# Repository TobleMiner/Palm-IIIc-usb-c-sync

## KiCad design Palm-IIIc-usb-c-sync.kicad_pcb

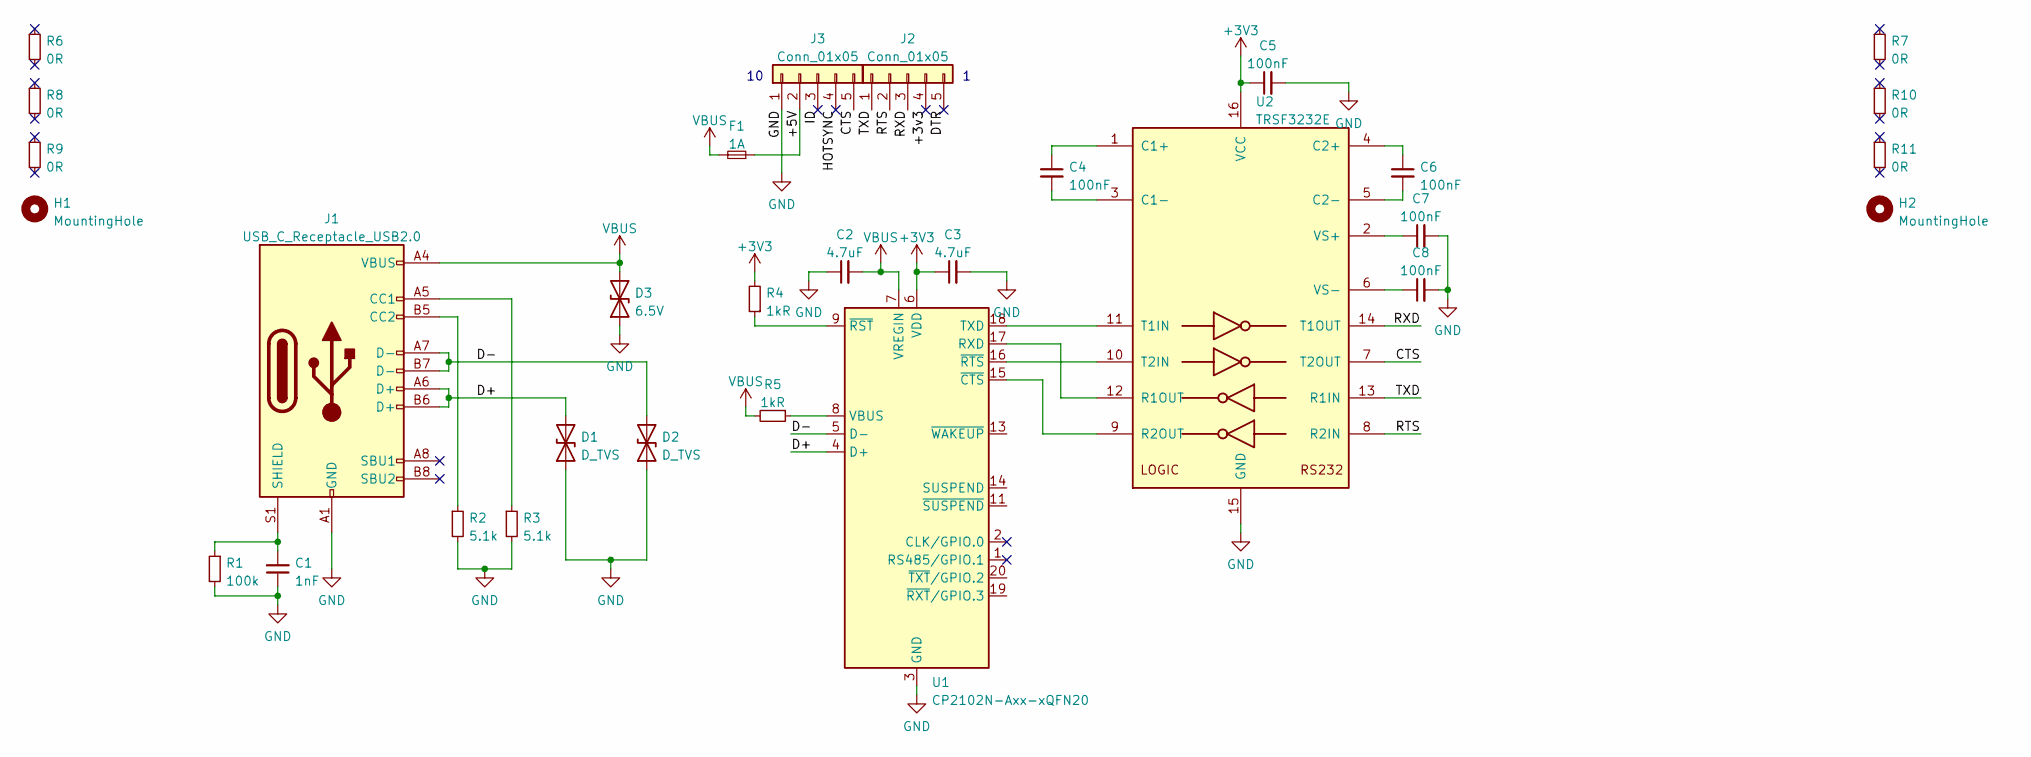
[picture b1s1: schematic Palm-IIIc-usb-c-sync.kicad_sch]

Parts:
C1: 1nF; C_0603_1608Metric; LCSC C1588
C2, C3: 4.7uF; C_0402_1005Metric; LCSC C23733
C4, C5, C6, C7, C8: 100nF; C_0402_1005Metric; LCSC C1525
D1, D2: D_TVS; C_0402_1005Metric; LCSC C125059
D3: 6.5V; D_SOD-523; LCSC C506103
F1: 1A; Fuse_0402_1005Metric; LCSC C424347
H1, H2: MountingHole; ToolingHole_JLCSMT
J1: USB_C_Receptacle_USB2.0; MC-311S; LCSC C2977718
J2, J3: Conn_01x05; 05x01_2mm
R1: 100k; R_0603_1608Metric; LCSC C25803
R2, R3: 5.1k; R_0402_1005Metric; LCSC C25905
R4, R5: 1kR; R_0402_1005Metric; LCSC C11702
R6, R7, R8, R9, R10, R11: 0R; R_0603_1608Metric; LCSC C21189
U1: CP2102N-Axx-xQFN20; SilivonLabs_QFN-20-1EP_3x3mm_P0.5mm_missing_pads; LCSC C969913
U2: TRSF3232E; TSSOP-16_4.4x5mm_P0.65mm; LCSC C2671080

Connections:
+3V3: C3.1, C5.1, R4.2, U1.6 (VDD), U2.16 (VCC)
/+3v3: J2.4
/+5V: F1.1, J3.2
/CTS: J3.5, U2.7 (T2OUT)
/D+: D1.2 (A2), J1.A6 (D+), J1.B6 (D+), U1.4 (D+)
/D-: D2.2 (A2), J1.A7 (D-), J1.B7 (D-), U1.5 (D-)
/DTR: J2.5
/HOTSYNC: J3.4
/ID: J3.3
/RTS: J2.2, U2.8 (R2IN)
/RXD: J2.3, U2.14 (T1OUT)
/TXD: J2.1, U2.13 (R1IN)
GND: C1.1, C2.1, C3.2, C5.2, C7.2, C8.2, D1.1 (A1), D2.1 (A1), D3.1 (A1), J1.A1 (GND), J1.A12 (GND), J1.B1 (GND), J1.B12 (GND), J3.1, R1.2, R2.2, R3.2, U1.3 (GND), U1.12 (GND), U1.21 (GND), U2.15 (GND)
unnamed: J1.A5 (CC1), R3.1
unnamed: J1.B5 (CC2), R2.1
unnamed: C1.2, J1.S1 (SHIELD), R1.1
unnamed: R5.1, U1.8 (VBUS)
unnamed: R4.1, U1.9 (~RST)
unnamed: U1.15 (~CTS), U2.9 (R2OUT)
unnamed: U1.16 (~RTS), U2.10 (T2IN)
unnamed: U1.17 (RXD), U2.12 (R1OUT)
unnamed: U1.18 (TXD), U2.11 (T1IN)
unnamed: C4.1, U2.1 (C1+)
unnamed: C7.1, U2.2 (VS+)
unnamed: C4.2, U2.3 (C1-)
unnamed: C6.1, U2.4 (C2+)
unnamed: C6.2, U2.5 (C2-)
unnamed: C8.1, U2.6 (VS-)
VBUS: C2.2, D3.2 (A2), F1.2, J1.A4 (VBUS), J1.A9 (VBUS), J1.B4 (VBUS), J1.B9 (VBUS), R5.2, U1.7 (VREGIN)

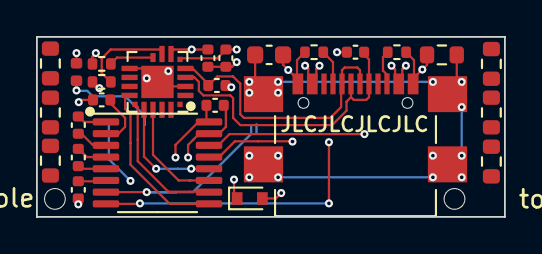
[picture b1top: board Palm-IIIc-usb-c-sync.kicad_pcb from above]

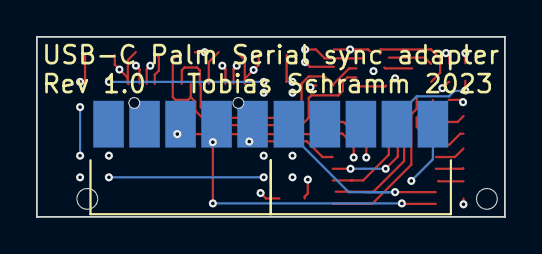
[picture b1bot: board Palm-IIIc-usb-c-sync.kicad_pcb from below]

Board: 4 copper layers, 26.0 x 10.0 mm, 30 parts (2 on the bottom side), 25 nets.

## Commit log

2023-02-13 Add manufacturing markings
2023-02-13 Hide all silkscreen designators
